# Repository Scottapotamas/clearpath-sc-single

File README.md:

# clearpath-sc-single

A cut down board with similar electronics to the Clearpath SC4-Hub, but designed for single motor use.

## Overview

The Clearpath line of CNC servo motors from Teknic are great for robotics due to tight integration of controller and motor.

The SC series are software controllable, but rely on the use of a communications hub for level shifting and e-stop etc. This hub is designed to handle 4 motors and daisy chaining, and offers outputs to control brake solenoids and e-stop switches.

My application is space constrained and has no brake, so this single channel board offers the same main functionality (but we lose e-stop and brake outputs, and less defensive filtering on power input) in a reduced form factor. The serial input and USB functionality is maintained, and all OEM level hardening/filtering on communication lines on the SC4 is maintained. 

12-24V input power to provide signal level power. USB to serial is powered from the USB host. Header supports other TTL level serial devices if desired.

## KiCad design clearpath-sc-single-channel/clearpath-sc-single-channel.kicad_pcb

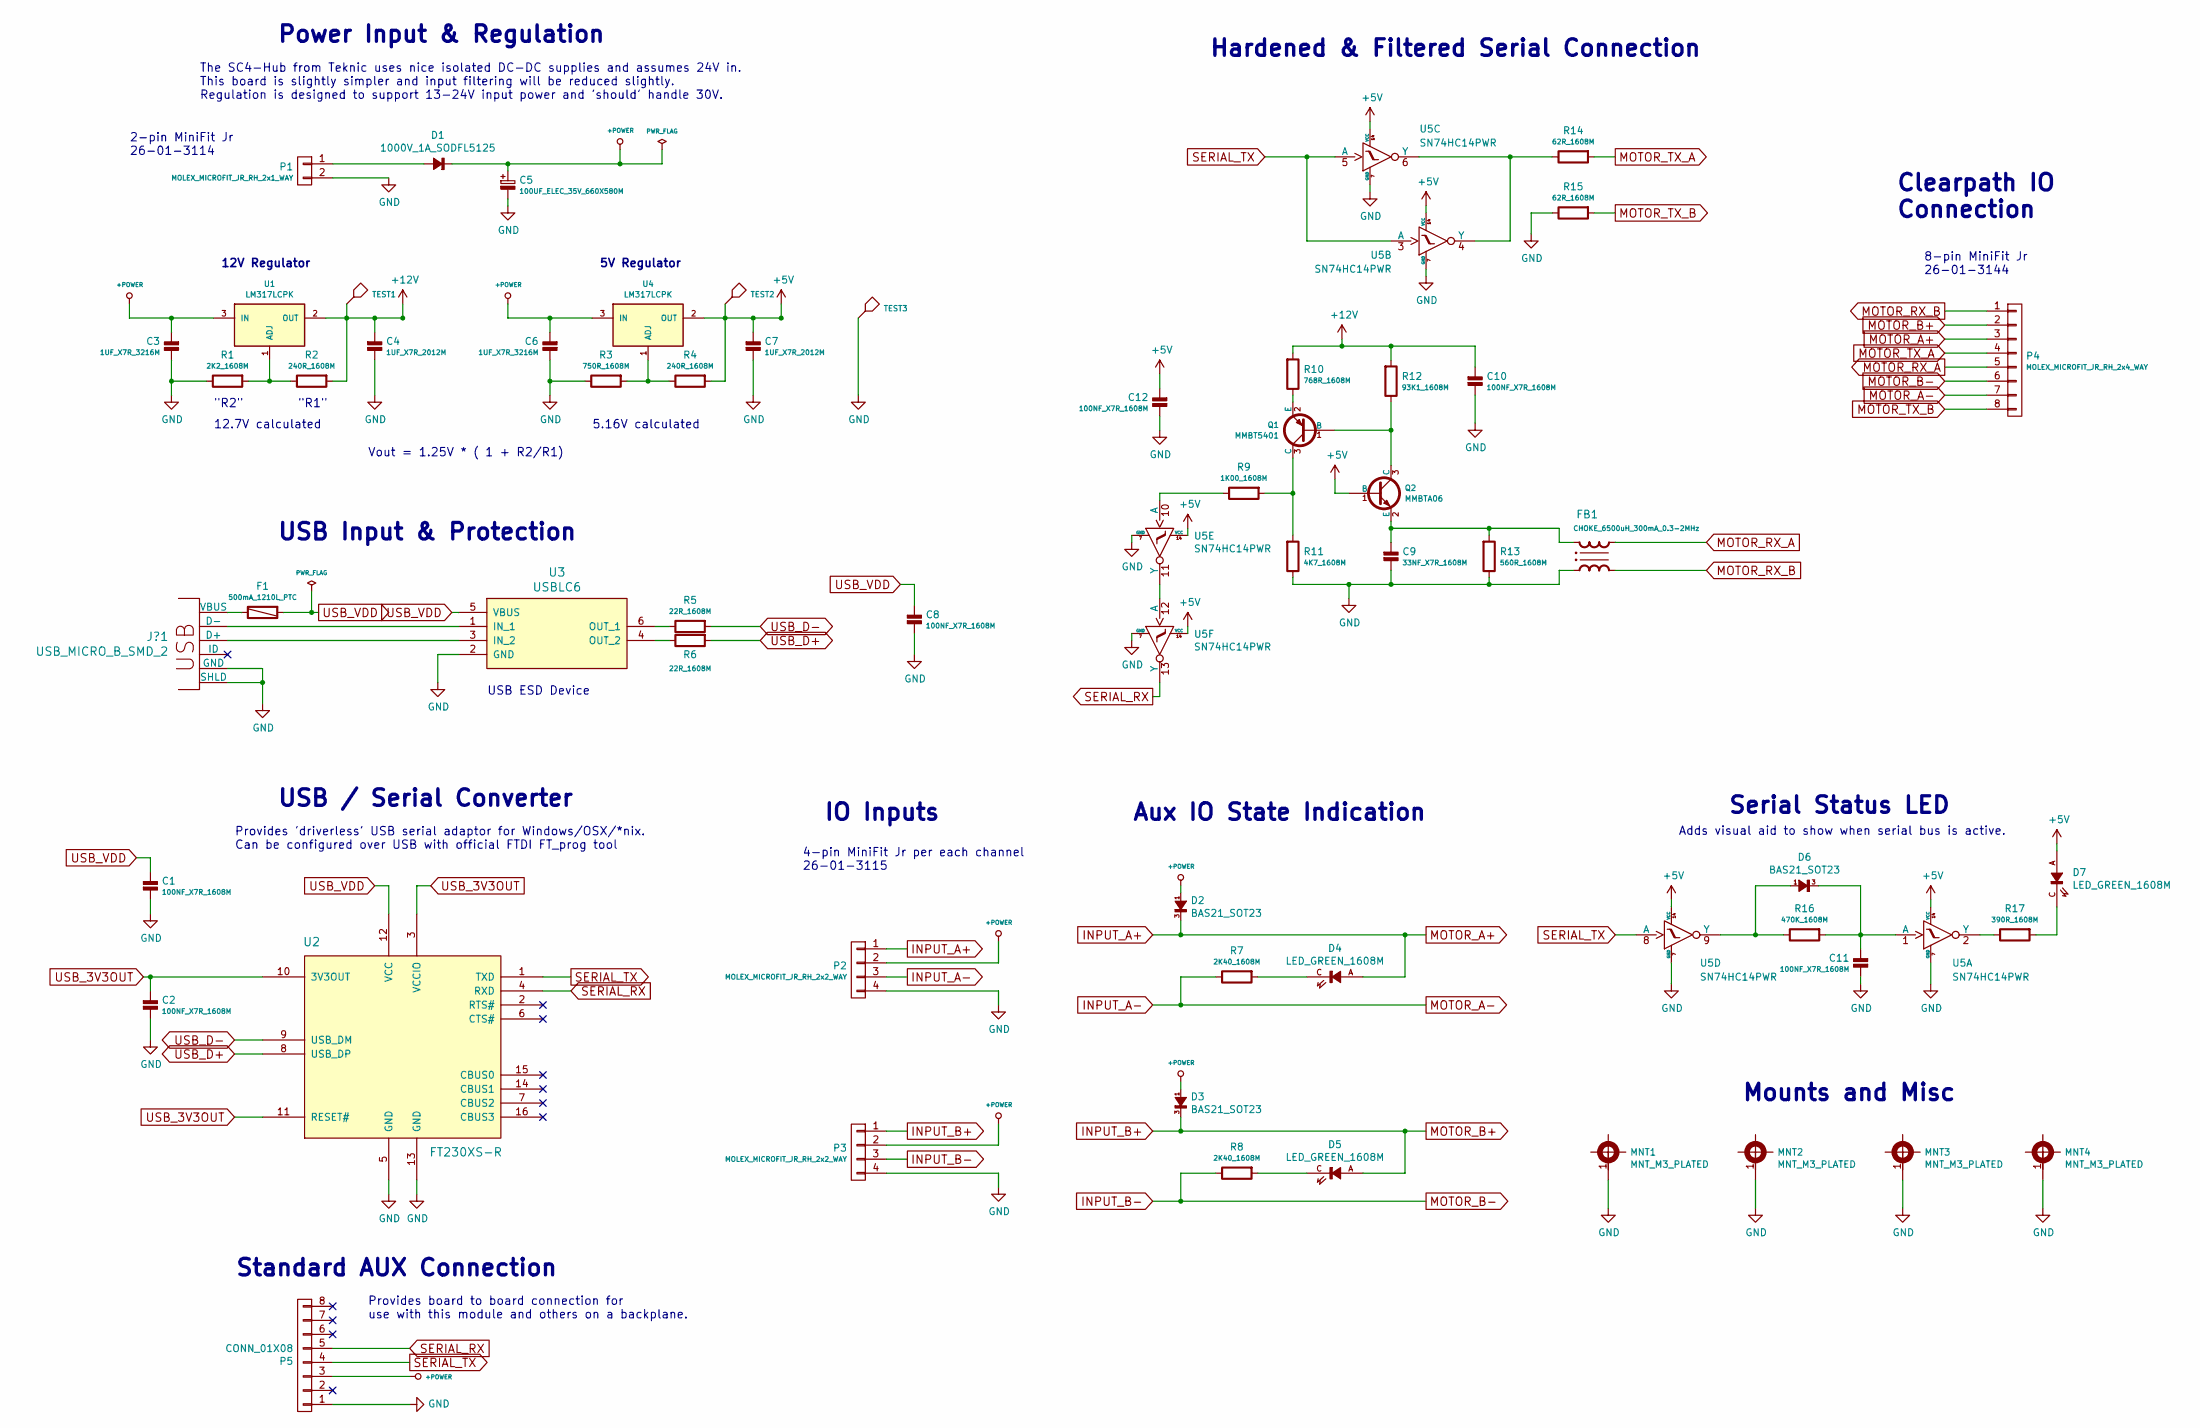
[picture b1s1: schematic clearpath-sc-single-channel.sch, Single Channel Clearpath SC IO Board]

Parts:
C1, C2, C8, C10, C11, C12: 100NF_X7R_1608M; CAPC1608X90N
C3, C6: 1UF_X7R_3216M; CAPC3216X135N
C4, C7: 1UF_X7R_2012M; CAPC2012X110N
C5: 100UF_ELEC_35V_660X580M; CAPAE660X580DD180L260N
C9: 33NF_X7R_1608M; CAPC1608X90N
D1: 1000V_1A_SODFL5125; SODFL5125X250N
D2, D3, D6: BAS21_SOT23; SOT95P240X110-3L16N
D4, D5, D7: LED_GREEN_1608M; LEDC1608X80L40N
F1: 500mA_1210L_PTC; FUSC3225X85L50N
FB1: CHOKE_6500uH_300mA_0.3-2MHz; SRF0905
J?1: USB_MICRO_B_SMD_2; MOLEX_47346-0001
MNT1, MNT2, MNT3, MNT4: MNT_M3_PLATED; MTGP650H330
P1: MOLEX_MICROFIT_JR_RH_2x1_WAY; Molex_MiniFit-JR-5569-02A2_2x01x4.20mm_Angled
P2, P3: MOLEX_MICROFIT_JR_RH_2x2_WAY; Molex_MiniFit-JR-5569-04A2_2x02x4.20mm_Angled
P4: MOLEX_MICROFIT_JR_RH_2x4_WAY; Molex_MiniFit-JR-5569-08A2_2x04x4.20mm_Angled
P5: CONN_01X08; 61300811121
Q1: MMBT5401; SOT95P240X110-3L16N
Q2: MMBTA06; SOT95P240X110-3L16N
R1: 2K2_1608M; RESC1608X50N
R2, R4: 240R_1608M; RESC1608X50N
R3: 750R_1608M; RESC1608X50N
R5, R6: 22R_1608M; RESC1608X50N
R7, R8: 2K40_1608M; RESC1608X50N
R9: 1K00_1608M; RESC1608X50N
R10: 768R_1608M; RESC1608X50N
R11: 4K7_1608M; RESC1608X50N
R12: 93K1_1608M; RESC1608X50N
R13: 560R_1608M; RESC1608X50N
R14, R15: 62R_1608M; RESC1608X50N
R16: 470K_1608M; RESC1608X50N
R17: 390R_1608M; RESC1608X50N
TEST1, TEST2: CLIP_HOOK_RED; KEYSTONE_5000
TEST3: CLIP_HOOK_BLACK; KEYSTONE_5001
U1, U4: LM317LCPK; SOT89N
U2: FT230XS-R; SOP16P65_500X640X120L62X24N
U3: USBLC6; SOT95P280X145-6L50N
U5: SN74HC14PWR; SOP14P65_500X640X120L62X24N

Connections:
+5V: C7.1, C12.1, D7.A, Q2.1 (B), R4.1, TEST2.1, U4.2 (OUT), U5.14 (VCC)
+12V: C4.1, C10.1, R2.1, R10.1, R12.1, TEST1.1, U1.2 (OUT)
+POWER: C3.1, C5.1, C6.1, D1.C, D2.1 (A), D3.1 (A), P2.2, P3.2, P5.3, U1.3 (IN), U4.3 (IN)
GND: C1.2, C2.2, C3.2, C4.2, C5.2, C6.2, C7.2, C8.2, C9.2, C10.2, C11.2, C12.2, FB1.1, J?1.5 (GND), J?1.SH (SHLD), MNT1.1, MNT2.1, MNT3.1, MNT4.1, P1.2, P2.4, P3.4, P5.1, R1.2, R3.2, R11.2, R13.2, R15.2, TEST3.1, U2.5 (GND), U2.13 (GND), U3.2 (GND), U5.7 (GND)
INPUT_A+: D2.3 (C), D4.A, P2.1, P4.3
INPUT_A-: P2.3, P4.7, R7.2
INPUT_B+: D3.3 (C), D5.A, P3.1, P4.2
INPUT_B-: P3.3, P4.6, R8.2
MOTOR_RX_A: FB1.3, P4.5
MOTOR_RX_B: FB1.4, P4.1
MOTOR_TX_A: P4.4, R14.1
MOTOR_TX_B: P4.8, R15.1
unnamed: C9.1, FB1.2, Q2.2 (E), R13.1
unnamed: C11.1, D6.3 (C), R16.1, U5.1 (A)
unnamed: D1.A, P1.1
unnamed: D4.C, R7.1
unnamed: D5.C, R8.1
unnamed: D6.1 (A), R16.2, U5.9 (Y)
unnamed: D7.C, R17.1
unnamed: F1.2, J?1.1 (VBUS)
unnamed: J?1.2 (D-), U3.1 (IN_1)
unnamed: J?1.3 (D+), U3.3 (IN_2)
unnamed: Q1.1 (B), Q2.3 (C), R12.2
unnamed: Q1.2 (E), R10.2
unnamed: Q1.3 (C), R9.1, R11.1
unnamed: R1.1, R2.2, U1.1 (ADJ)
unnamed: R3.1, R4.2, U4.1 (ADJ)
unnamed: R5.2, U3.6 (OUT_1)
unnamed: R6.2, U3.4 (OUT_2)
unnamed: R9.2, U5.10 (A)
unnamed: R14.2, U5.4 (Y), U5.6 (Y)
unnamed: R17.2, U5.2 (Y)
unnamed: U5.11 (Y), U5.12 (A)
SERIAL_RX: P5.5, U2.4 (RXD), U5.13 (Y)
SERIAL_TX: P5.4, U2.1 (TXD), U5.3 (A), U5.5 (A), U5.8 (A)
USB_3V3OUT: C2.1, U2.3 (VCCIO), U2.10 (3V3OUT), U2.11 (RESET#)
USB_D+: R6.1, U2.8 (USB_DP)
USB_D-: R5.1, U2.9 (USB_DM)
USB_VDD: C1.1, C8.1, F1.1, U2.12 (VCC), U3.5 (VBUS)

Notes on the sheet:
USB Input & Protection
Clearpath IO Connection
IO Inputs
4-pin MiniFit Jr per each channel 26-01-3115
Power Input & Regulation
2-pin MiniFit Jr 26-01-3114
8-pin MiniFit Jr 26-01-3144
Mounts and Misc
Hardened & Filtered Serial Connection
Aux IO State Indication
Serial Status LED
USB / Serial Converter
Adds visual aid to show when serial bus is active.
USB ESD Device
Provides 'driverless' USB serial adaptor for Windows/OSX/*nix. Can be configured over USB with official FTDI FT_prog tool
The SC4-Hub from Teknic uses nice isolated DC-DC supplies and assumes 24V in. This board is slightly simpler and input filtering will be reduced slightly. Regulation is designed to support 13-24V input power and 'should' handle 30V.
12V Regulator
5V Regulator
"R1"
"R2"
Vout = 1.25V * ( 1 + R2/R1)
12.7V calculated
5.16V calculated
Standard AUX Connection
Provides board to board connection for use with this module and others on a backplane.

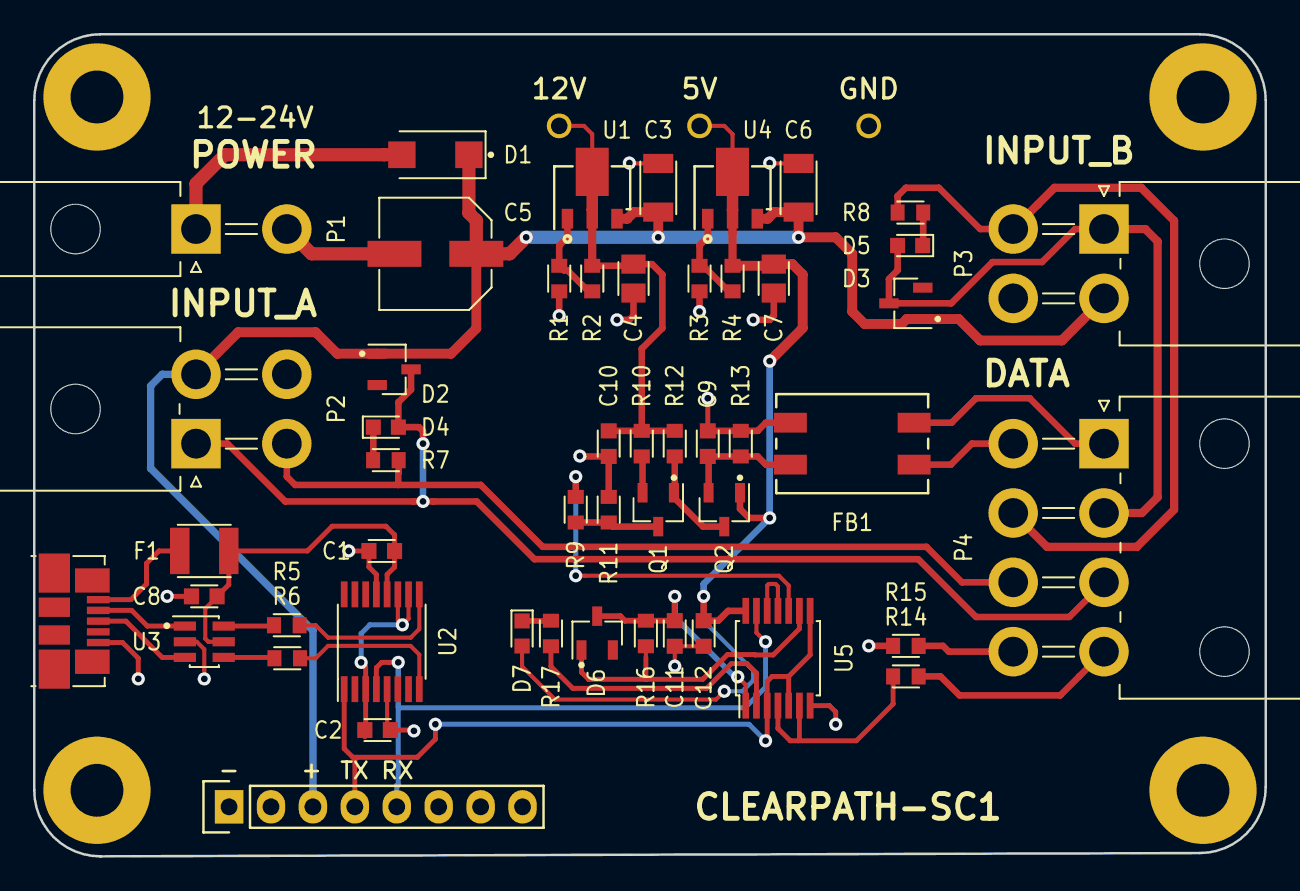
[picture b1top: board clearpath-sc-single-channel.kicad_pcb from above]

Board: 2 copper layers, 74.6 x 49.8 mm, 58 parts (0 on the bottom side), 39 nets.

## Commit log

2017-09-24 Initial pass at schematic
    Most connectors and filter/protection circuitry sch captured.
    Needs USB-TTL adaptor and power stuff still.
2017-09-25 Added serial and regulator ICs
    FT230 series USB TTL IC added, 12 and 5V linear regs added.
    Reorganised some content and fixed label directions.
2017-09-25 Regulator and input circuits finished.
    Added pdf of current sch and updated readme.
2017-09-27 Annotated and DRC checks
    Fixed some DRC warnings.
2017-09-27 Full footprint association, netlist generation
    DRC passes with no errors, ready for layout.
2017-09-27 Started routing
    Placement complete, most signal routing done or nearly finished.
2017-09-27 Reworked hex inverter and finished routing
    Increased trace thickness, all drc errors removed, improved hex schmitt wiring by shuffling unit allocation in schematic.
2017-09-27 Cosmetic improvements
    Added silkscreen text and voltage test points
2017-09-28 Added aux connector, silkscreen labels and some final touches.
    Ready for final check (pinout against SC4) and fab outputs
2017-09-28 Resolved missing 3d models on connector and line filter footprints. Exported PCB pdf
2017-09-28 Added renders
2017-09-28 Fleshed out readme with images
    Also rewrote text a bit.
2017-09-29 Shrunk board outline slightly to improve tolerances
    Useful if mated to a backplane, would allow two within a 100mm long edge area.
2017-10-06 Added BoM
2017-10-06 Added gerbers
2017-10-09 Fixed gap in outline layer, exported gerbers
    Fixes issue where copper layers don't export properly.
